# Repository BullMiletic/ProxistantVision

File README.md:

# ProxistantVision
Source files for BULL.MILETIC's installation [Proxistant Vision](https://bull.miletic.info/research/proxistant-vision).

Read about [Ferriscope](https://bull.miletic.info/works/ferriscope)

Read about [Venetie](https://bull.miletic.info/works/venetie-11111100001)

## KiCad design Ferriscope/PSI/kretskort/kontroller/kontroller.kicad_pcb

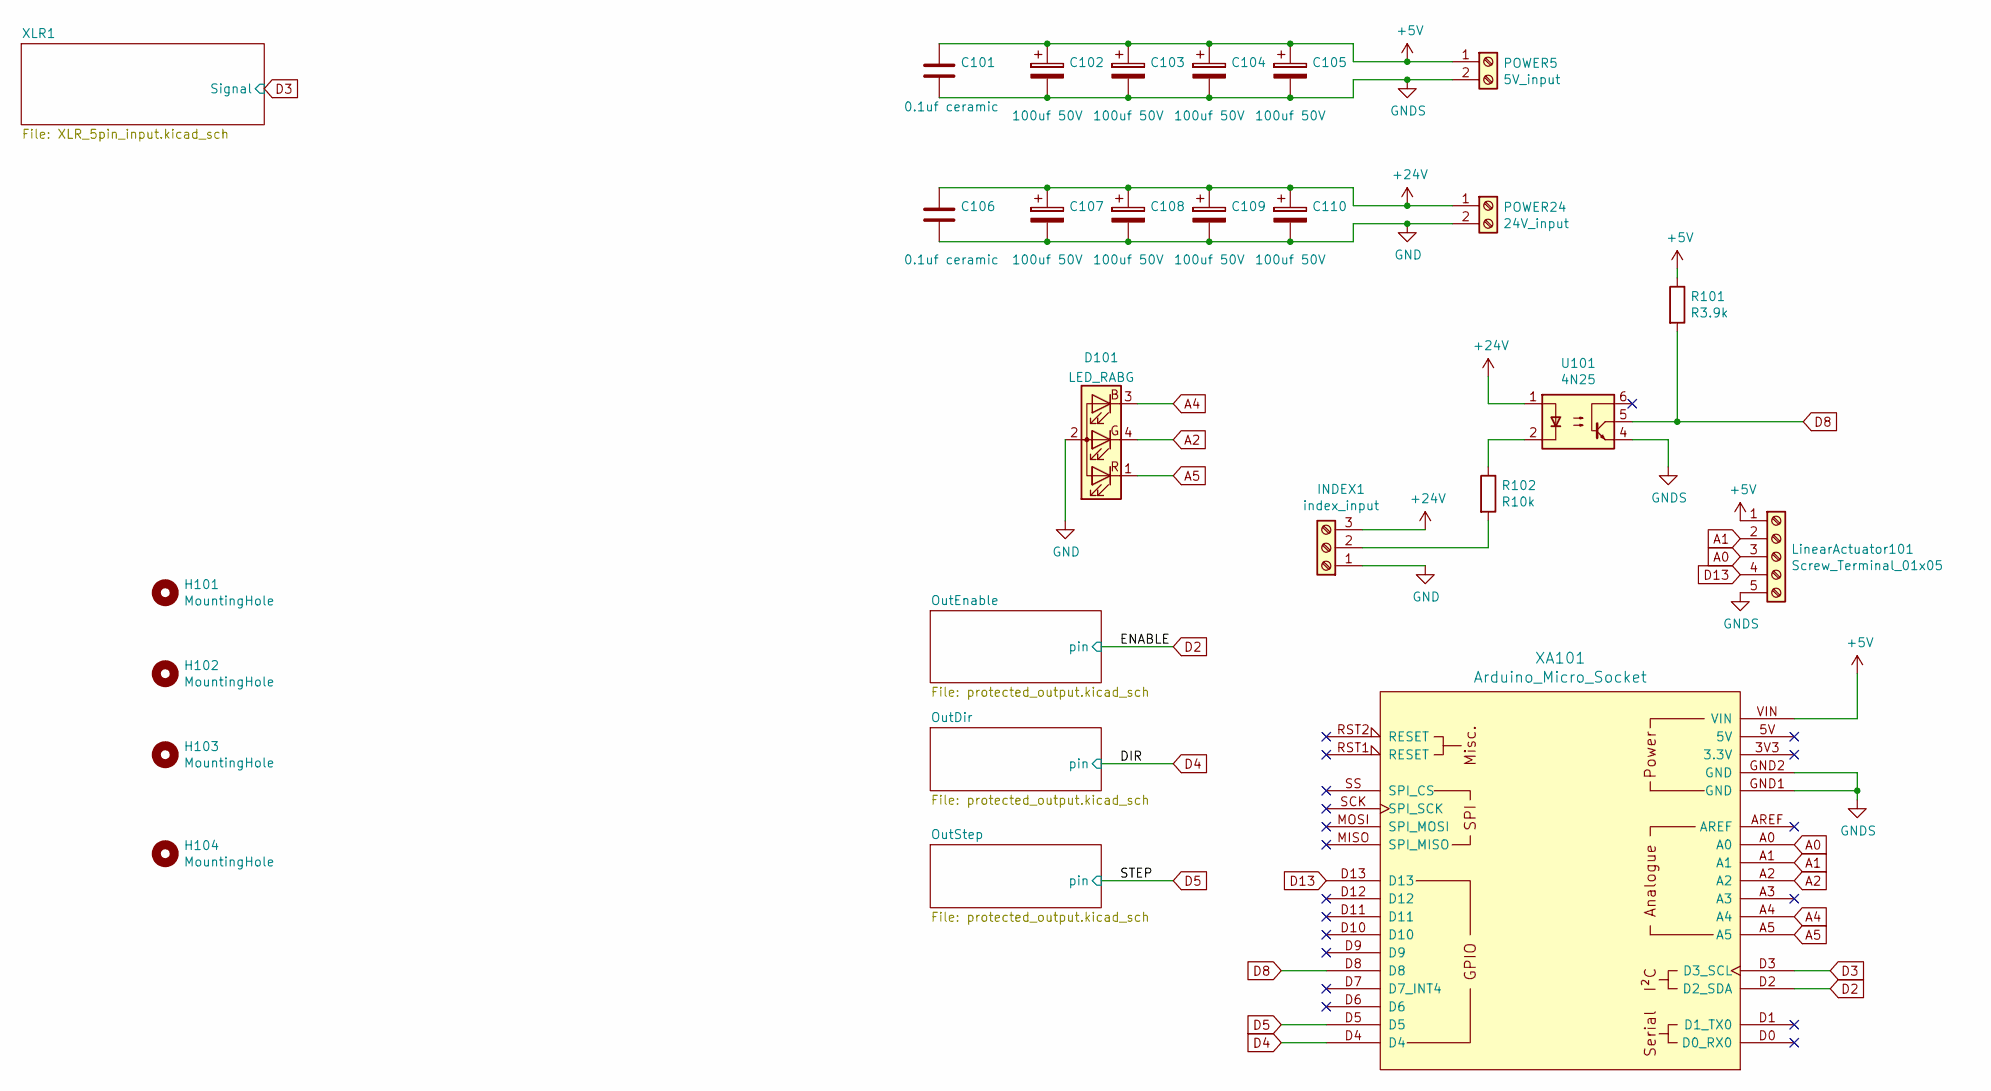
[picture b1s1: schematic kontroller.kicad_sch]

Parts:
C101, C106: 0.1uf ceramic; C_Disc_D5.0mm_W2.5mm_P5.00mm; MPN C322C104K5R5TA
C102, C103, C104, C105, C107, C108, C109, C110: 100uf 50V; CP_Radial_D10.0mm_P2.50mm; MPN ECE-A1HN101U
D101: LED_RABG; LED_D5.0mm-4_RGB
H101, H102, H103, H104: MountingHole; MountingHole_4.3mm_M4_DIN965_Pad
INDEX1: index_input; TerminalBlock_Phoenix_MKDS-1,5-3-5.08_1x03_P5.08mm_Horizont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; MPN 1729131
LinearActuator101: Screw_Terminal_01x05; TerminalBlock_Phoenix_MKDS-1,5-5-5.08_1x05_P5.08mm_Horizont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; MPN 1729157
POWER5: 5V_input; TerminalBlock_Phoenix_MKDS-1,5-2-5.08_1x02_P5.08mm_Horizont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; MPN 1729128
POWER24: 24V_input; TerminalBlock_Phoenix_MKDS-1,5-2-5.08_1x02_P5.08mm_Horizont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; MPN 1729128
R101: R3.9k; R_Axial_DIN0204_L3.6mm_D1.6mm_P5.08mm_Horizontal
R102: R10k; R_Axial_DIN0204_L3.6mm_D1.6mm_P5.08mm_Horizontal
U101: 4N25; DIP-6_W7.62mm
XA101: Arduino_Micro_Socket

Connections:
+5V: C101.1, C102.1, C103.1, C104.1, C105.1, LinearActuator101.1, POWER5.1, R101.1, XA101.VIN; also elsewhere on the board
+24V: C106.1, C107.1, C108.1, C109.1, C110.1, INDEX1.3, POWER24.1, U101.1; also elsewhere on the board
A0: LinearActuator101.3, XA101.A0
A1: LinearActuator101.2, XA101.A1
A2: D101.4 (GK), XA101.A2
A4: D101.3 (BK), XA101.A4
A5: D101.1 (RK), XA101.A5
D2: XA101.D2 (D2_SDA); also elsewhere on the board
D3: XA101.D3 (D3_SCL); also elsewhere on the board
D8: R101.2, U101.5, XA101.D8
D13: LinearActuator101.4, XA101.D13
GND: C106.2, C107.2, C108.2, C109.2, C110.2, D101.2 (A), INDEX1.1, POWER24.2; also elsewhere on the board
GNDS: C101.2, C102.2, C103.2, C104.2, C105.2, LinearActuator101.5, POWER5.2, U101.4, XA101.GND1 (GND), XA101.GND2 (GND); also elsewhere on the board
unnamed: INDEX1.2, R102.2
unnamed: R102.1, U101.2

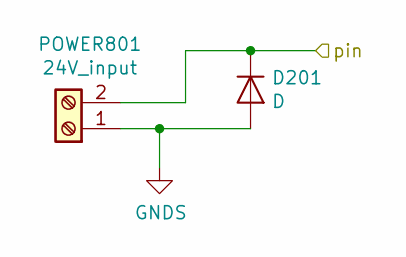
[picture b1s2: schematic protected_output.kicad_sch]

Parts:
D201: D; D_DO-15_P10.16mm_Horizontal; MPN SA5.0A
POWER801: 24V_input; TerminalBlock_Phoenix_MKDS-1,5-2-5.08_1x02_P5.08mm_Horizont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; MPN 1729128

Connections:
GNDS: D201.2 (A), POWER801.1; also elsewhere on the board

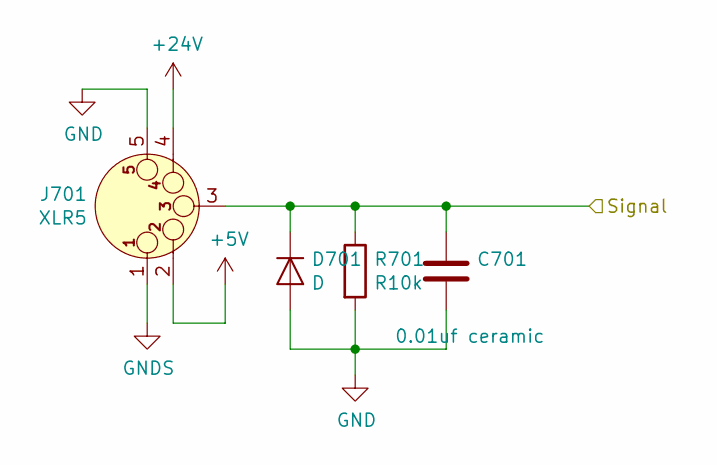
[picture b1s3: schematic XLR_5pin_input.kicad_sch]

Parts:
C701: 0.01uf ceramic; C_Disc_D5.0mm_W2.5mm_P5.00mm; MPN 10000PF
D701: D; D_DO-15_P10.16mm_Horizontal; MPN SA5.0A
J701: XLR5; IO-XLR5-M-EH; MPN IO-XLR5-M-EH
R701: R10k; R_Axial_DIN0204_L3.6mm_D1.6mm_P5.08mm_Horizontal

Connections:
+5V: J701.2; also elsewhere on the board
+24V: J701.4 (P3); also elsewhere on the board
D3: C701.1, D701.1 (K), J701.3, R701.1; also elsewhere on the board
GND: C701.2, D701.2 (A), J701.5, R701.2; also elsewhere on the board
GNDS: J701.1; also elsewhere on the board

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
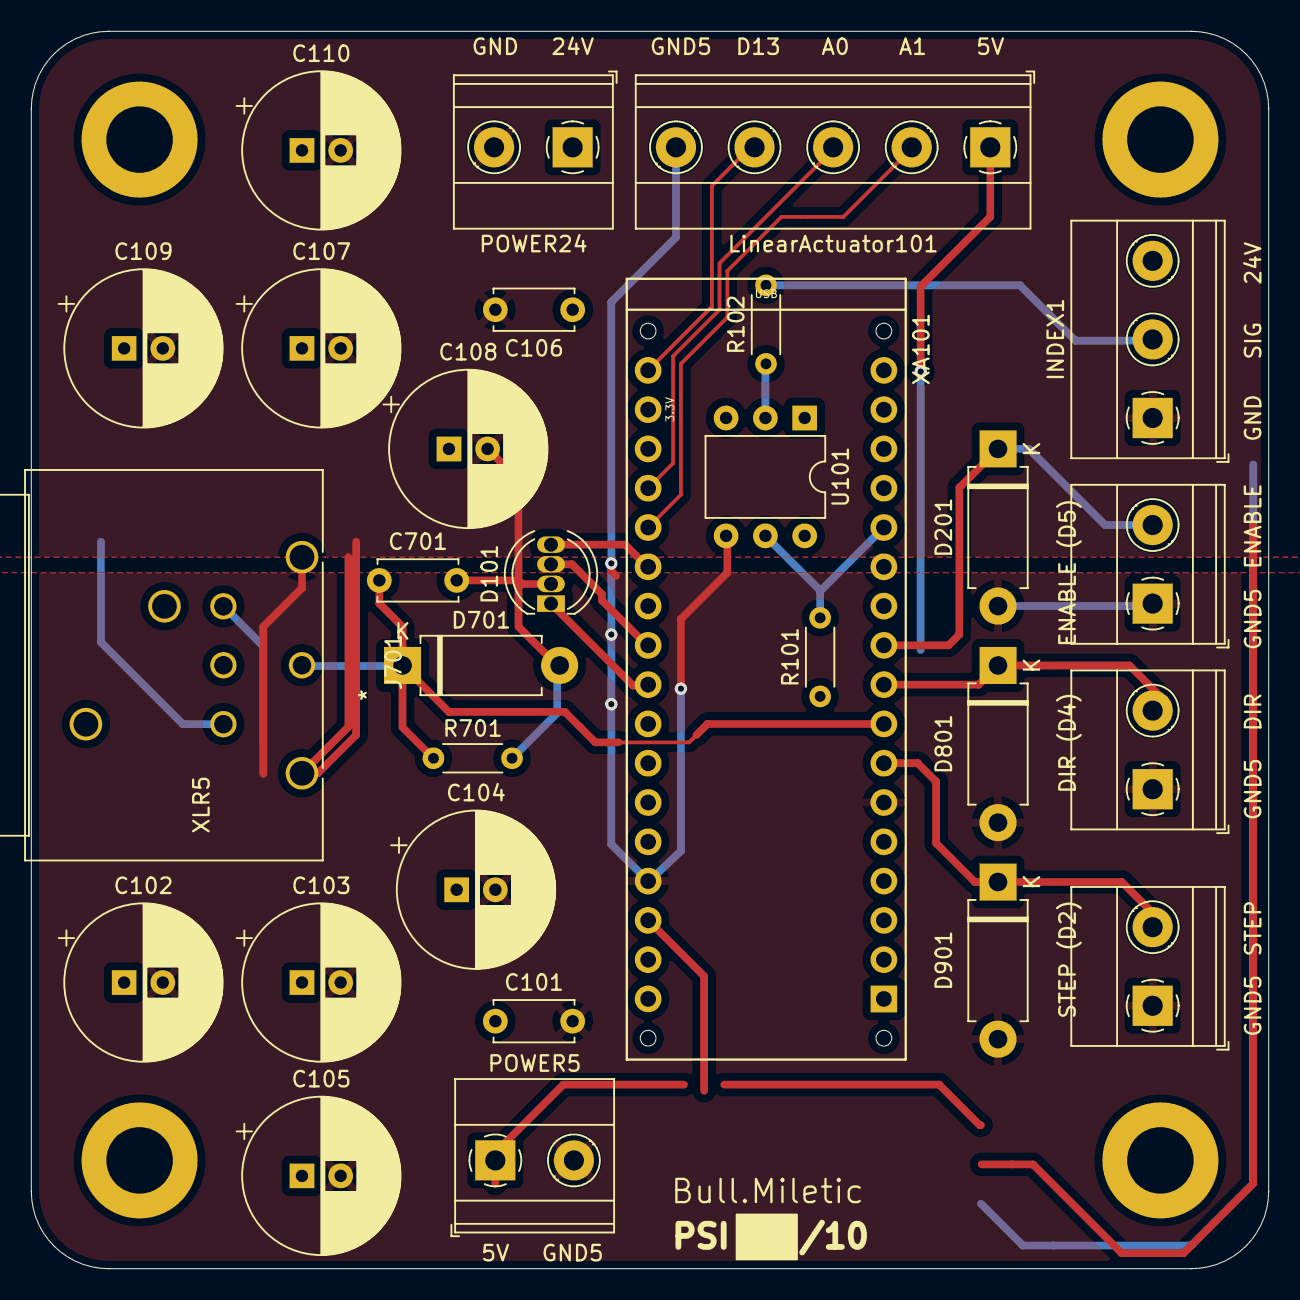
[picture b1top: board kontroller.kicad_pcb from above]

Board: 2 copper layers, 80.0 x 80.0 mm, 33 parts (0 on the bottom side), 17 nets.

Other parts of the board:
D801, D901: D; D_DO-15_P10.16mm_Horizontal
OUT201, OUT501: 24V_input; TerminalBlock_Phoenix_MKDS-1,5-2-5.08_1x02_P5.08mm_Horizont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

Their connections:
D2: D901.1 (K), OUT501.2; also elsewhere on the board
GNDS: D801.2 (A), D901.2 (A), OUT201.1, OUT501.1; also elsewhere on the board

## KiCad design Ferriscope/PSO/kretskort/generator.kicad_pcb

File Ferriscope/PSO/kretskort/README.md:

# Generator
Tar lyd som input og sender ut 5 signaler basert på FFT.

## Errata

### Versjon 1.0
- Mangler merking av +/- på power inputs

## Output fra shield med Magnus sin firmware
På oppstart - S1 flimrer litt

Signal_1 = LOW  152	Signal_2 = HIGH  277	Signal_3 = HIGH  578	Signal_4 = HIGH  1004	Signal_5 = HIGH  1013
Signal_1 = LOW  144	Signal_2 = HIGH  348	Signal_3 = HIGH  744	Signal_4 = HIGH  1010	Signal_5 = HIGH  868
Signal_1 = LOW  133	Signal_2 = HIGH  295	Signal_3 = HIGH  615	Signal_4 = HIGH  965	Signal_5 = HIGH  993
Signal_1 = LOW  133	Signal_2 = HIGH  249	Signal_3 = HIGH  512	Signal_4 = HIGH  827	Signal_5 = HIGH  1007
Signal_1 = LOW  130	Signal_2 = HIGH  212	Signal_3 = HIGH  427	Signal_4 = HIGH  708	Signal_5 = HIGH  1015

På slutten og på starten:

Signal_1 = LOW  59	Signal_2 = LOW  59	Signal_3 = LOW  72	Signal_4 = LOW  82	Signal_5 = LOW  124
Signal_1 = LOW  59	Signal_2 = LOW  62	Signal_3 = LOW  73	Signal_4 = LOW  72	Signal_5 = LOW  125
Signal_1 = LOW  60	Signal_2 = LOW  65	Signal_3 = LOW  74	Signal_4 = LOW  76	Signal_5 = LOW  115
Signal_1 = LOW  54	Signal_2 = LOW  64	Signal_3 = LOW  75	Signal_4 = LOW  77	Signal_5 = LOW  130

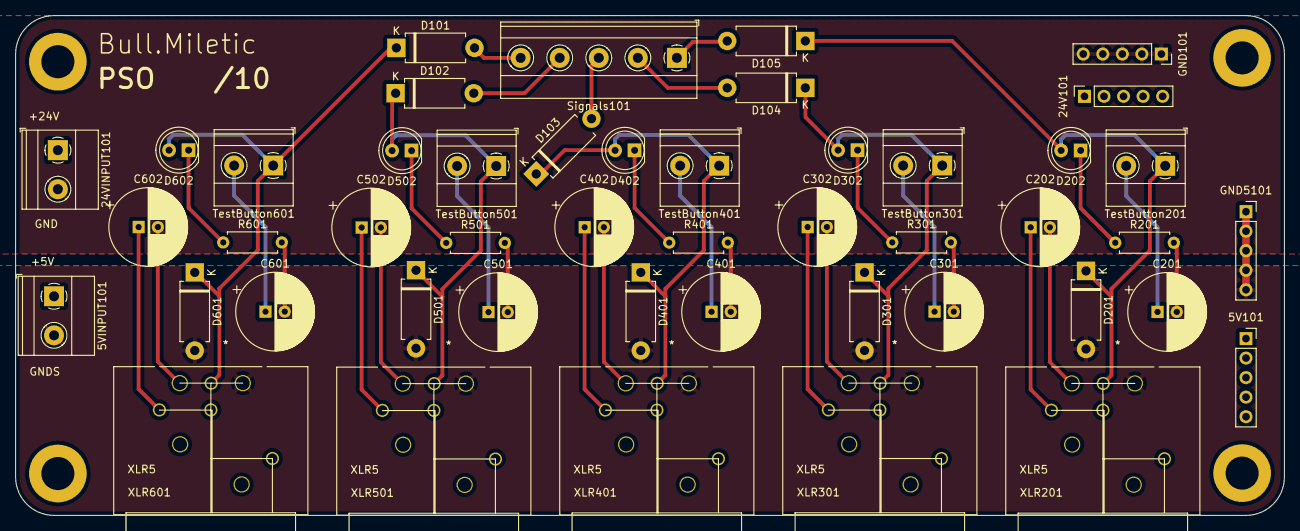
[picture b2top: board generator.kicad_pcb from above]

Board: 2 copper layers, 165.0 x 65.0 mm, 52 parts (0 on the bottom side), 19 nets.

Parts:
5V101: 5V; PinSocket_1x05_P2.54mm_Vertical
5VINPUT101: 5VINPUT; TerminalBlock_Phoenix_MKDS-1,5-2-5.08_1x02_P5.08mm_Horizont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
24V101: 24V; PinSocket_1x05_P2.54mm_Vertical
24VINPUT101: 24VINPUT; TerminalBlock_Phoenix_MKDS-1,5-2-5.08_1x02_P5.08mm_Horizont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
C201, C202, C301, C302, C401, C402, C501, C502, C601, C602: CP; CP_Radial_D10.0mm_P2.50mm
D101, D102, D103, D104, D105, D201, D301, D401, D501, D601: D; D_DO-15_P10.16mm_Horizontal
D202, D302, D402, D502, D602: LED; LED_D5.0mm
GND101: GND; PinSocket_1x05_P2.54mm_Vertical
GND5101: GND5; PinSocket_1x05_P2.54mm_Vertical
H101, H102, H103, H104: MountingHole; MountingHole_4.3mm_M4_DIN965_Pad
H105: Image; globe
R201, R301, R401, R501, R601: 4.7R; R_Axial_DIN0207_L6.3mm_D2.5mm_P7.62mm_Horizontal
Signals101: Signal; TerminalBlock_Phoenix_MKDS-1,5-5-5.08_1x05_P5.08mm_Horizont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
TestButton201, TestButton301, TestButton401, TestButton501, TestButton601: Button; TerminalBlock_Phoenix_MKDS-1,5-2-5.08_1x02_P5.08mm_Horizont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
XLR201, XLR301, XLR401, XLR501, XLR601: XLR5; IO-XLR5-F-EH

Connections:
+5V: 5V101.1, 5V101.2, 5V101.3, 5V101.4, 5V101.5, 5VINPUT101.1, C201.1, C301.1, C401.1, C501.1, C601.1, TestButton201.2, TestButton301.2, TestButton401.2, TestButton501.2, TestButton601.2, XLR201.2, XLR301.2, XLR401.2, XLR501.2, XLR601.2
+24V: 24V101.1, 24V101.2, 24V101.3, 24V101.4, 24V101.5, 24VINPUT101.1, C202.1, C302.1, C402.1, C502.1, C602.1, XLR201.4 (P3), XLR301.4 (P3), XLR401.4 (P3), XLR501.4 (P3), XLR601.4 (P3)
GND: 24VINPUT101.2, C202.2, C302.2, C402.2, C502.2, C602.2, GND101.1, GND101.2, GND101.3, GND101.4, GND101.5, XLR201.5, XLR301.5, XLR401.5, XLR501.5, XLR601.5
GNDS: 5VINPUT101.2, C201.2, C301.2, C401.2, C501.2, C601.2, D201.2 (A), D301.2 (A), D401.2 (A), D501.2 (A), D601.2 (A), GND5101.1, GND5101.2, GND5101.3, GND5101.4, GND5101.5, R201.2, R301.2, R401.2, R501.2, R601.2, XLR201.1, XLR301.1, XLR401.1, XLR501.1, XLR601.1
unnamed: D202.1 (K), R201.1
unnamed: D302.1 (K), R301.1
unnamed: D402.1 (K), R401.1
unnamed: D502.1 (K), R501.1
unnamed: D602.1 (K), R601.1
unnamed: D105.2 (A), Signals101.1
unnamed: D104.2 (A), Signals101.2
unnamed: D103.2 (A), Signals101.3
unnamed: D102.2 (A), Signals101.4
unnamed: D101.2 (A), Signals101.5
S1: D105.1 (K), D201.1 (K), D202.2 (A), TestButton201.1, XLR201.3
S2: D104.1 (K), D301.1 (K), D302.2 (A), TestButton301.1, XLR301.3
S3: D103.1 (K), D401.1 (K), D402.2 (A), TestButton401.1, XLR401.3
S4: D102.1 (K), D501.1 (K), D502.2 (A), TestButton501.1, XLR501.3
S5: D101.1 (K), D601.1 (K), D602.2 (A), TestButton601.1, XLR601.3

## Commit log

2022-08-10 Source files backup for easy sharing
2022-08-16 Create STEP
2022-09-20 Timer tweaks + support for pot to adjust speed
2022-09-28 new defaults
2022-10-25 With last adjustments to index position

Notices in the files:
parts and their libraries:
Copyright 2021 Accelerated Designs. All rights reserved.
